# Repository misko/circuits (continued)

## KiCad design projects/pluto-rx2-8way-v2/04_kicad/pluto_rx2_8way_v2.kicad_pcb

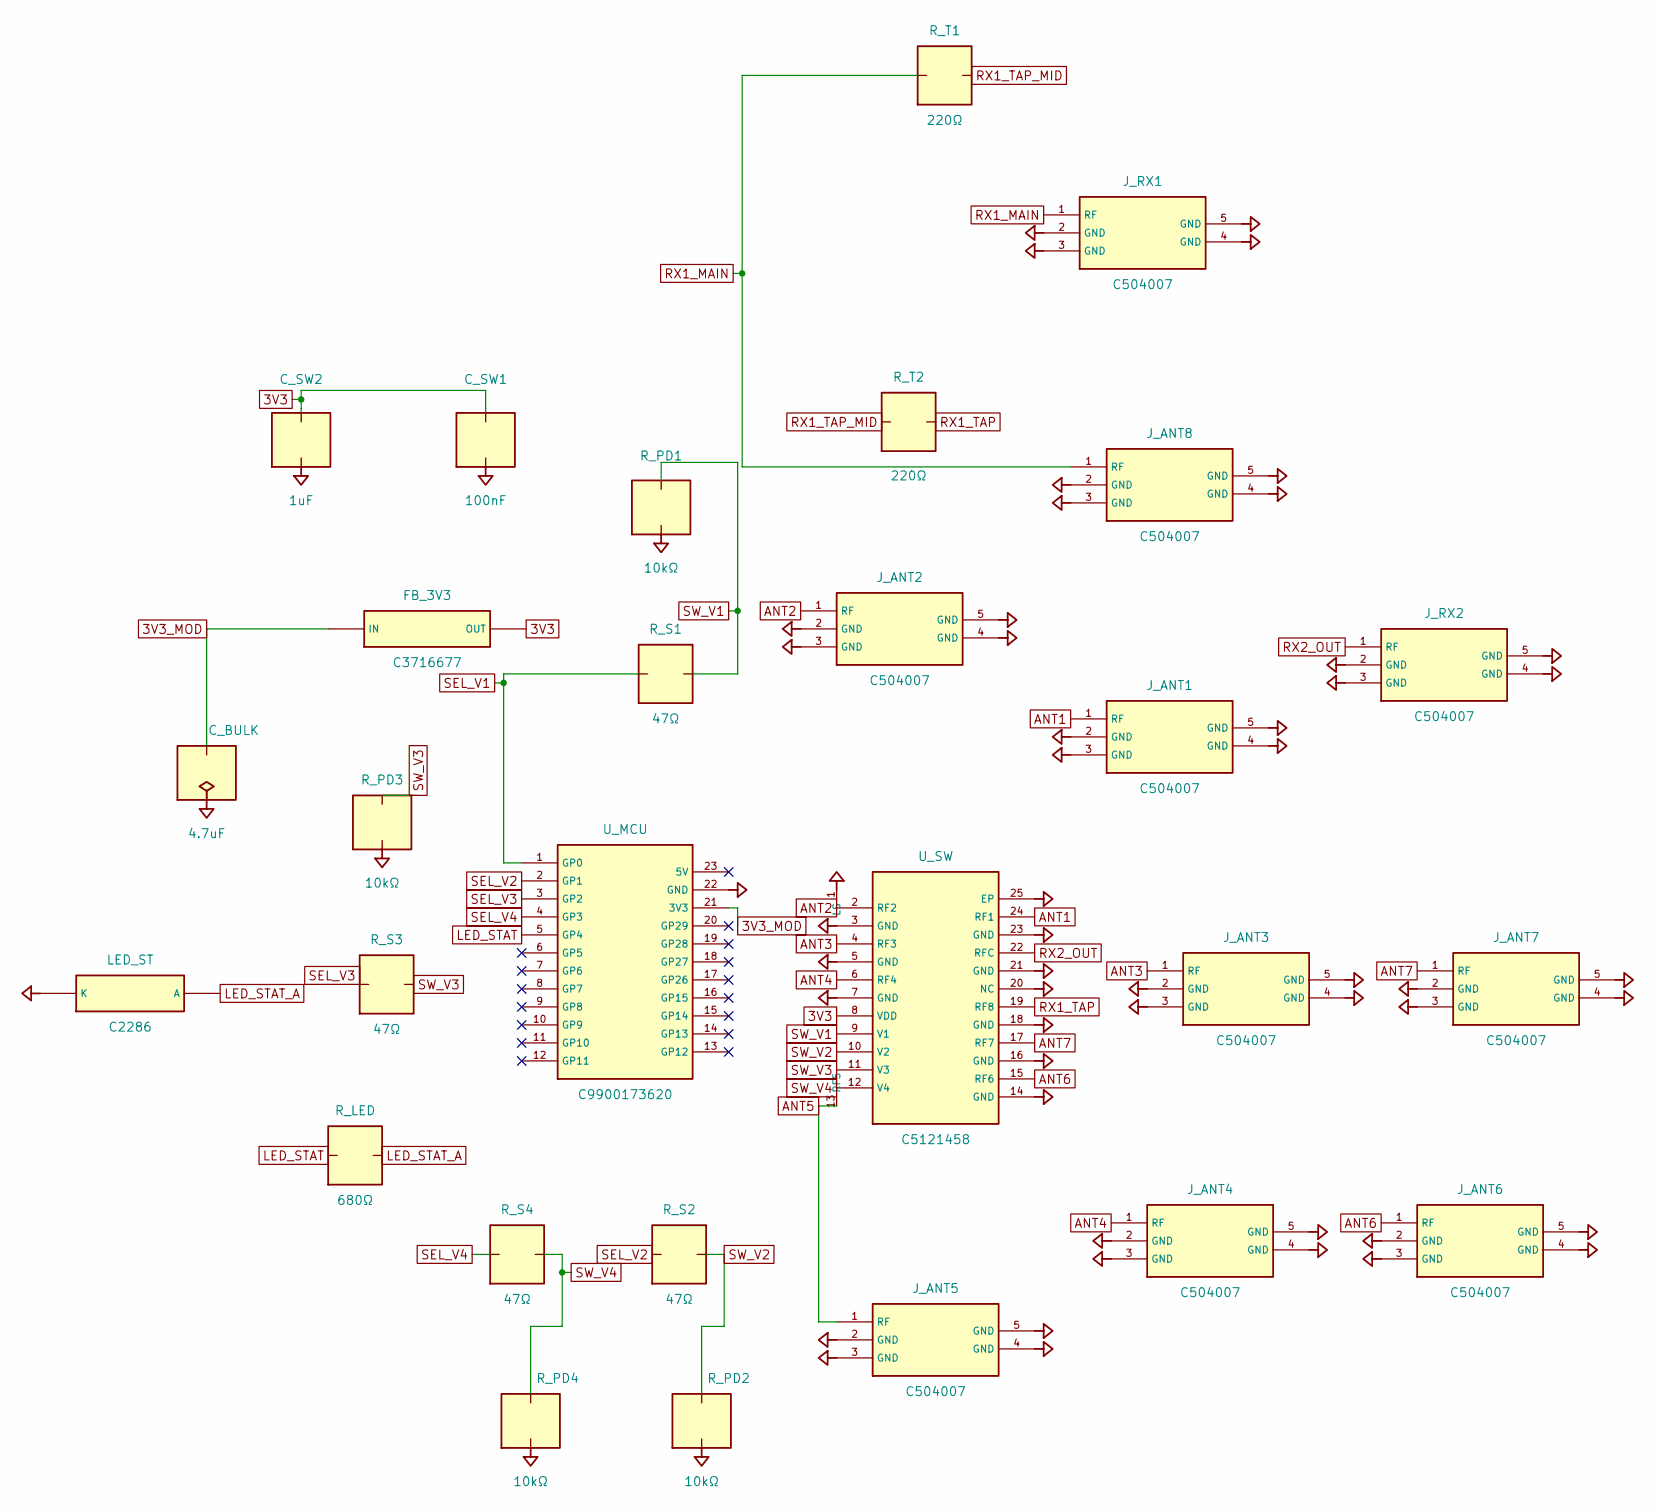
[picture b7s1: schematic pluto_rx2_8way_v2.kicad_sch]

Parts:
C_BULK: 4.7uF; C_0805_2012Metric
C_SW1: 100nF; C_0402_1005Metric
C_SW2: 1uF; C_0603_1608Metric
FB_3V3: C3716677; L_0805_2012Metric
J_ANT1, J_ANT2, J_ANT3, J_ANT4, J_ANT5, J_ANT6, J_ANT7, J_ANT8: C504007; SMA_Vertical_5.08sq_D1.4
J_RX1, J_RX2: C504007; SMA_Vertical_5.08sq_D1.4
LED_ST: C2286; LED_0603_1608Metric
R_LED: 680Ω; R_0402_1005Metric
R_PD1, R_PD2, R_PD3, R_PD4: 10kΩ; R_0402_1005Metric
R_S1, R_S2, R_S3, R_S4: 47Ω; R_0402_1005Metric
R_T1, R_T2: 220Ω; R_0402_1005Metric
U_MCU: C9900173620; RP2040_Zero_LCC23_18x23.5
U_SW: C5121458; QFN-24_4x4_P0.5_EP2.7_PE42482

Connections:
3V3: C_SW1.1, C_SW2.1, FB_3V3.2 (OUT), U_SW.8 (VDD)
3V3_MOD: C_BULK.1, FB_3V3.1 (IN), U_MCU.21 (3V3)
ANT1: J_ANT1.1 (RF), U_SW.24 (RF1)
ANT2: J_ANT2.1 (RF), U_SW.2 (RF2)
ANT3: J_ANT3.1 (RF), U_SW.4 (RF3)
ANT4: J_ANT4.1 (RF), U_SW.6 (RF4)
ANT5: J_ANT5.1 (RF), U_SW.13 (RF5)
ANT6: J_ANT6.1 (RF), U_SW.15 (RF6)
ANT7: J_ANT7.1 (RF), U_SW.17 (RF7)
GND: C_BULK.2, C_SW1.2, C_SW2.2, J_ANT1.2 (GND), J_ANT1.3 (GND), J_ANT1.4 (GND), J_ANT1.5 (GND), J_ANT2.2 (GND), J_ANT2.3 (GND), J_ANT2.4 (GND), J_ANT2.5 (GND), J_ANT3.2 (GND), J_ANT3.3 (GND), J_ANT3.4 (GND), J_ANT3.5 (GND), J_ANT4.2 (GND), J_ANT4.3 (GND), J_ANT4.4 (GND), J_ANT4.5 (GND), J_ANT5.2 (GND), J_ANT5.3 (GND), J_ANT5.4 (GND), J_ANT5.5 (GND), J_ANT6.2 (GND), J_ANT6.3 (GND), J_ANT6.4 (GND), J_ANT6.5 (GND), J_ANT7.2 (GND), J_ANT7.3 (GND), J_ANT7.4 (GND), J_ANT7.5 (GND), J_ANT8.2 (GND), J_ANT8.3 (GND), J_ANT8.4 (GND), J_ANT8.5 (GND), J_RX1.2 (GND), J_RX1.3 (GND), J_RX1.4 (GND), J_RX1.5 (GND), J_RX2.2 (GND), J_RX2.3 (GND), J_RX2.4 (GND), J_RX2.5 (GND), LED_ST.1 (K), R_PD1.2, R_PD2.2, R_PD3.2, R_PD4.2, U_MCU.22 (GND), U_SW.1 (LS), U_SW.3 (GND), U_SW.5 (GND), U_SW.7 (GND), U_SW.14 (GND), U_SW.16 (GND), U_SW.18 (GND), U_SW.20 (NC), U_SW.21 (GND), U_SW.23 (GND), U_SW.25 (EP)
LED_STAT: R_LED.1, U_MCU.5 (GP4)
LED_STAT_A: LED_ST.2 (A), R_LED.2
RX1_MAIN: J_ANT8.1 (RF), J_RX1.1 (RF), R_T1.1
RX1_TAP: R_T2.2, U_SW.19 (RF8)
RX1_TAP_MID: R_T1.2, R_T2.1
RX2_OUT: J_RX2.1 (RF), U_SW.22 (RFC)
SEL_V1: R_S1.1, U_MCU.1 (GP0)
SEL_V2: R_S2.1, U_MCU.2 (GP1)
SEL_V3: R_S3.1, U_MCU.3 (GP2)
SEL_V4: R_S4.1, U_MCU.4 (GP3)
SW_V1: R_PD1.1, R_S1.2, U_SW.9 (V1)
SW_V2: R_PD2.1, R_S2.2, U_SW.10 (V2)
SW_V3: R_PD3.1, R_S3.2, U_SW.11 (V3)
SW_V4: R_PD4.1, R_S4.2, U_SW.12 (V4)

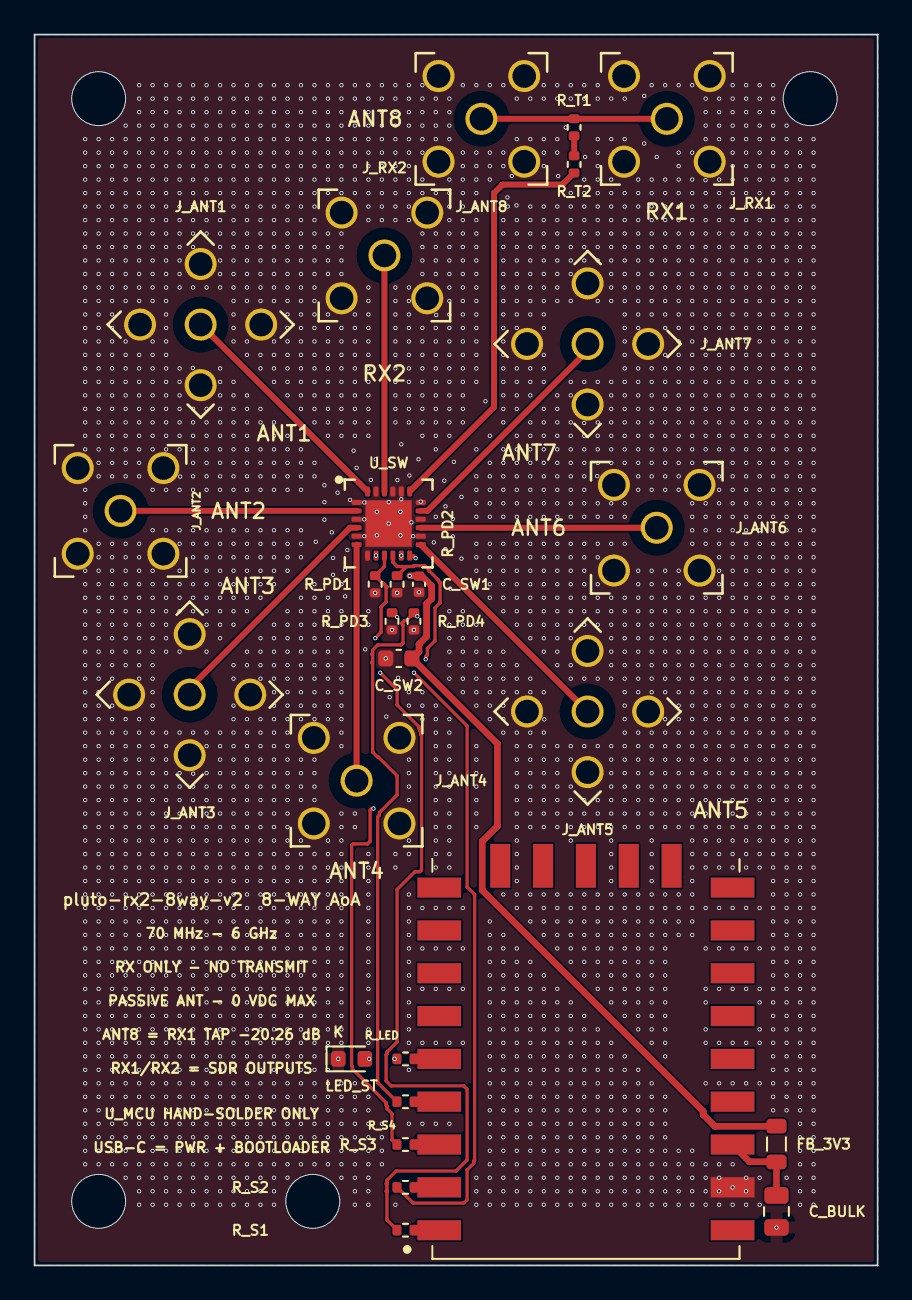
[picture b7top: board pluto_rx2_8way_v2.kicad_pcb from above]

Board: 4 copper layers, 50.0 x 73.0 mm, 32 parts (0 on the bottom side), 24 nets.

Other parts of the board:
H1, H2, H3, H4: MountingHole_3.2mm_M3

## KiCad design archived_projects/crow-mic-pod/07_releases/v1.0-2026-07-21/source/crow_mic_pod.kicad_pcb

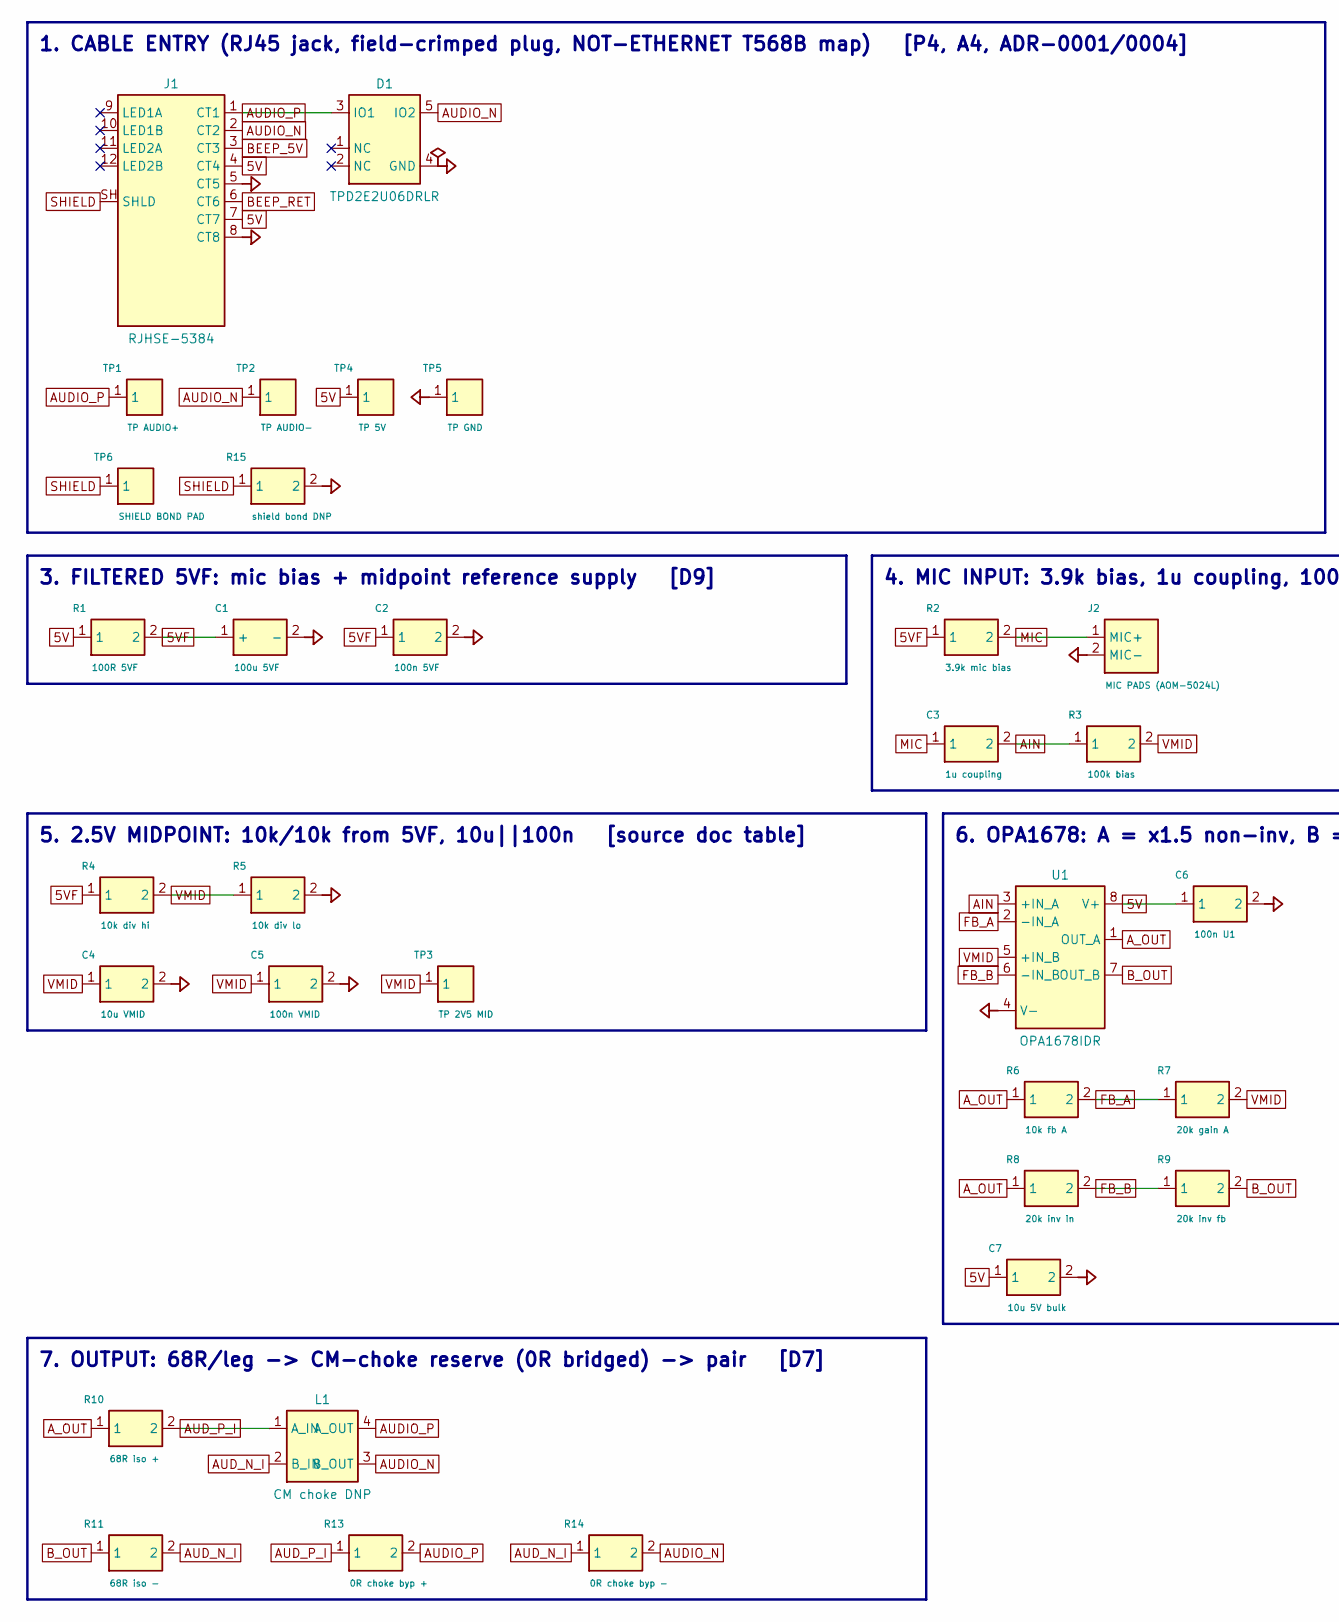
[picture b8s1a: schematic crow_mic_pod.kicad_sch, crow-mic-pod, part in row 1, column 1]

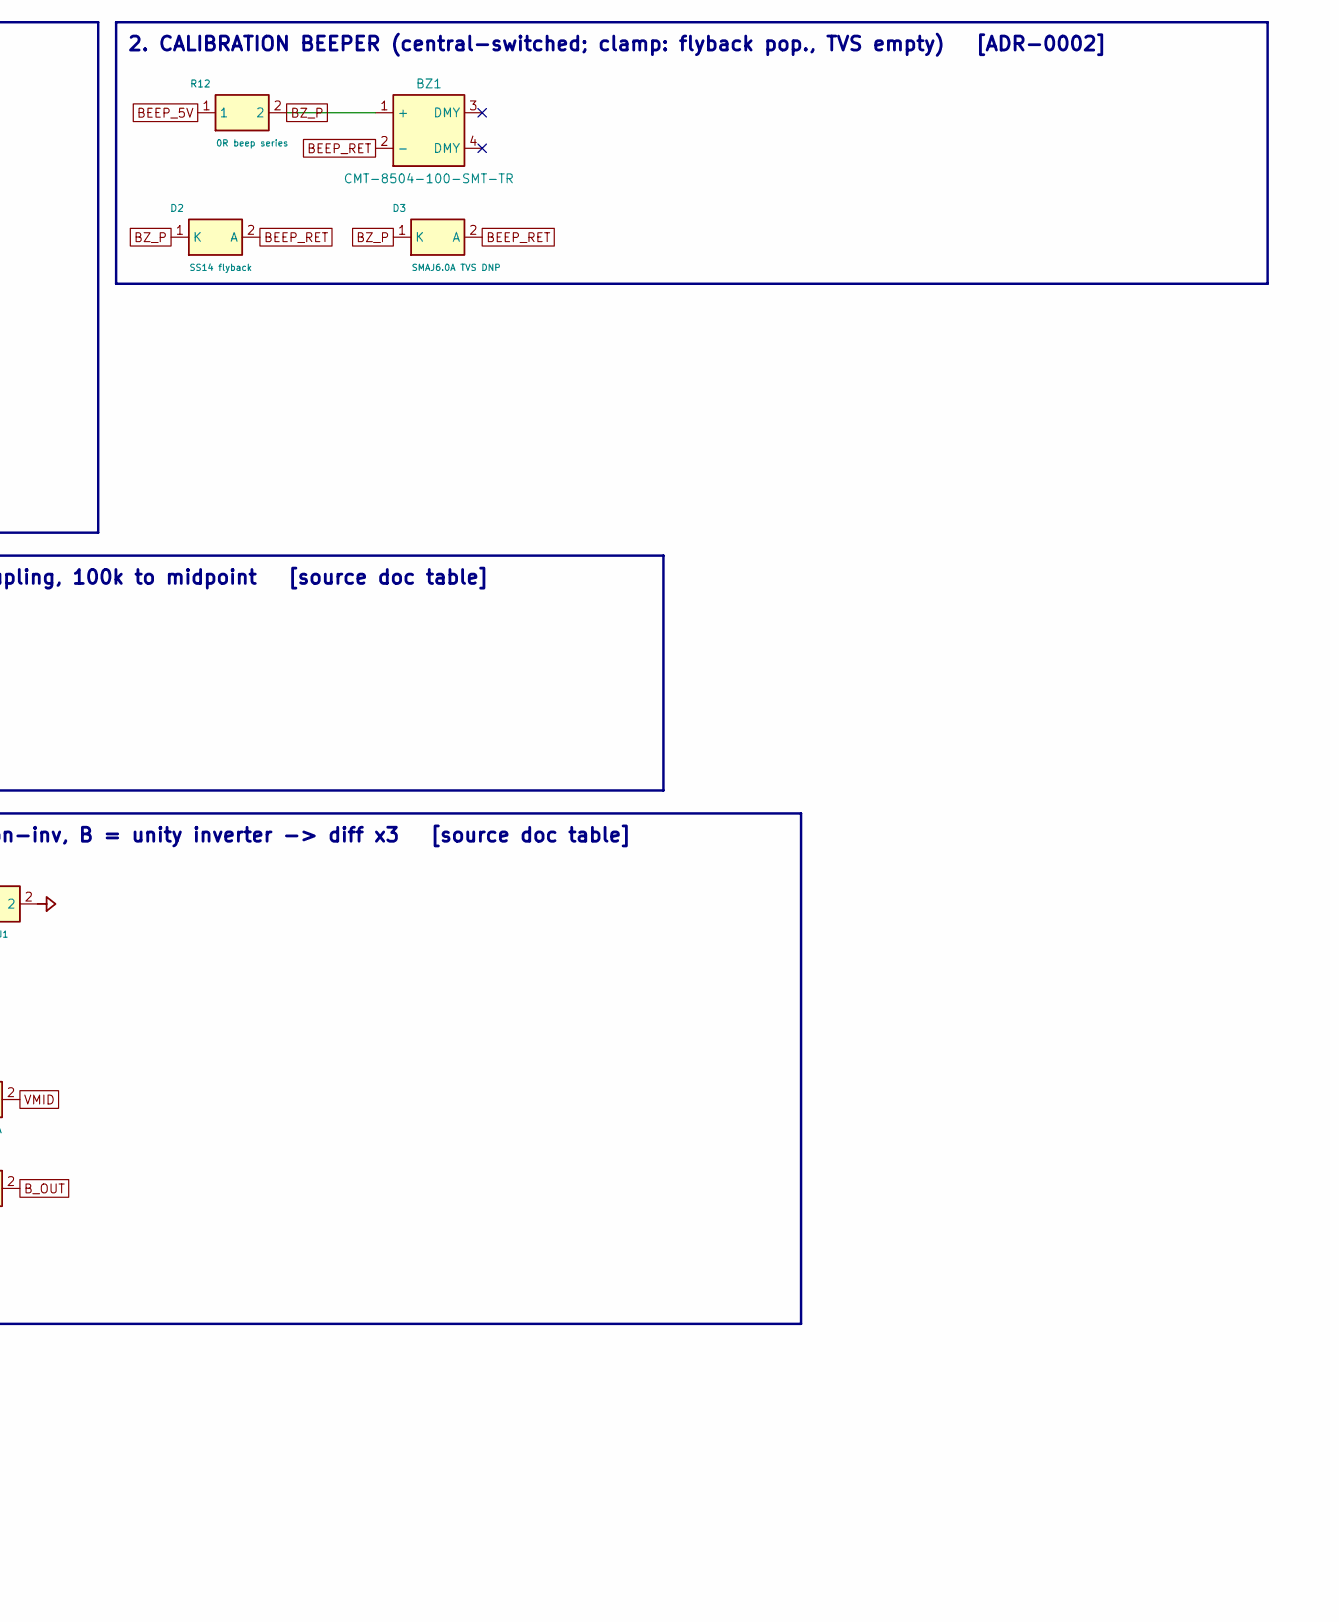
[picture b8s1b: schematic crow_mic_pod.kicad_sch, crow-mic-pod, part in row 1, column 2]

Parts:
BZ1: CMT-8504-100-SMT-TR; CMT-8504
C1: 100u 5VF; CP_Elec_6.3x5.4
C2: 100n 5VF; C_0805_2012Metric
C3: 1u coupling; C_0805_2012Metric
C4: 10u VMID; C_0805_2012Metric
C5: 100n VMID; C_0805_2012Metric
C6: 100n U1; C_0805_2012Metric
C7: 10u 5V bulk; C_0805_2012Metric
D1: TPD2E2U06DRLR; SOT-553
D2: SS14 flyback; D_SMA
D3: SMAJ6.0A TVS DNP; D_SMA
J1: RJHSE-5384; RJ45_Amphenol_RJHSE538X
J2: MIC PADS (AOM-5024L); PinHeader_1x02_P2.54mm_Vertical
L1: CM choke DNP; L_CommonMode_Wuerth_WE-SL2
R1: 100R 5VF; R_0805_2012Metric
R2: 3.9k mic bias; R_0805_2012Metric
R3: 100k bias; R_0805_2012Metric
R4: 10k div hi; R_0805_2012Metric
R5: 10k div lo; R_0805_2012Metric
R6: 10k fb A; R_0805_2012Metric
R7: 20k gain A; R_0805_2012Metric
R8: 20k inv in; R_0805_2012Metric
R9: 20k inv fb; R_0805_2012Metric
R10: 68R iso +; R_0805_2012Metric
R11: 68R iso -; R_0805_2012Metric
R12: 0R beep series; R_0805_2012Metric
R13: 0R choke byp +; R_0805_2012Metric
R14: 0R choke byp -; R_0805_2012Metric
R15: shield bond DNP; R_0805_2012Metric
TP1: TP AUDIO+; TestPoint_Pad_D1.5mm
TP2: TP AUDIO-; TestPoint_Pad_D1.5mm
TP3: TP 2V5 MID; TestPoint_Pad_D1.5mm
TP4: TP 5V; TestPoint_Pad_D1.5mm
TP5: TP GND; TestPoint_Pad_D1.5mm
TP6: SHIELD BOND PAD; TestPoint_Pad_D2.5mm
U1: OPA1678IDR; SOIC-8_3.9x4.9mm_P1.27mm

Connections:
5V: C6.1, C7.1, J1.4 (CT4), J1.7 (CT7), R1.1, TP4.1, U1.8 (V+)
5VF: C1.1 (+), C2.1, R1.2, R2.1, R4.1
AIN: C3.2, R3.1, U1.3 (+IN_A)
AUDIO_N: D1.5 (IO2), J1.2 (CT2), L1.3 (B_OUT), R14.2, TP2.1
AUDIO_P: D1.3 (IO1), J1.1 (CT1), L1.4 (A_OUT), R13.2, TP1.1
AUD_N_I: L1.2 (B_IN), R11.2, R14.1
AUD_P_I: L1.1 (A_IN), R10.2, R13.1
A_OUT: R6.1, R8.1, R10.1, U1.1 (OUT_A)
BEEP_5V: J1.3 (CT3), R12.1
BEEP_RET: BZ1.2 (-), D2.2 (A), D3.2 (A), J1.6 (CT6)
BZ_P: BZ1.1 (+), D2.1 (K), D3.1 (K), R12.2
B_OUT: R9.2, R11.1, U1.7 (OUT_B)
FB_A: R6.2, R7.1, U1.2 (-IN_A)
FB_B: R8.2, R9.1, U1.6 (-IN_B)
GND: C1.2 (-), C2.2, C4.2, C5.2, C6.2, C7.2, D1.4 (GND), J1.5 (CT5), J1.8 (CT8), J2.2 (MIC-), R5.2, R15.2, TP5.1, U1.4 (V-)
MIC: C3.1, J2.1 (MIC+), R2.2
SHIELD: J1.SH (SHLD), R15.1, TP6.1
VMID: C4.1, C5.1, R3.2, R4.2, R5.1, R7.2, TP3.1, U1.5 (+IN_B)

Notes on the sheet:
1. CABLE ENTRY (RJ45 jack, field-crimped plug, NOT-ETHERNET T568B map) [P4, A4, ADR-0001/0004]
2. CALIBRATION BEEPER (central-switched; clamp: flyback pop., TVS empty) [ADR-0002]
3. FILTERED 5VF: mic bias + midpoint reference supply [D9]
4. MIC INPUT: 3.9k bias, 1u coupling, 100k to midpoint [source doc table]
5. 2.5V MIDPOINT: 10k/10k from 5VF, 10u||100n [source doc table]
6. OPA1678: A = x1.5 non-inv, B = unity inverter -> diff x3 [source doc table]
7. OUTPUT: 68R/leg -> CM-choke reserve (0R bridged) -> pair [D7]

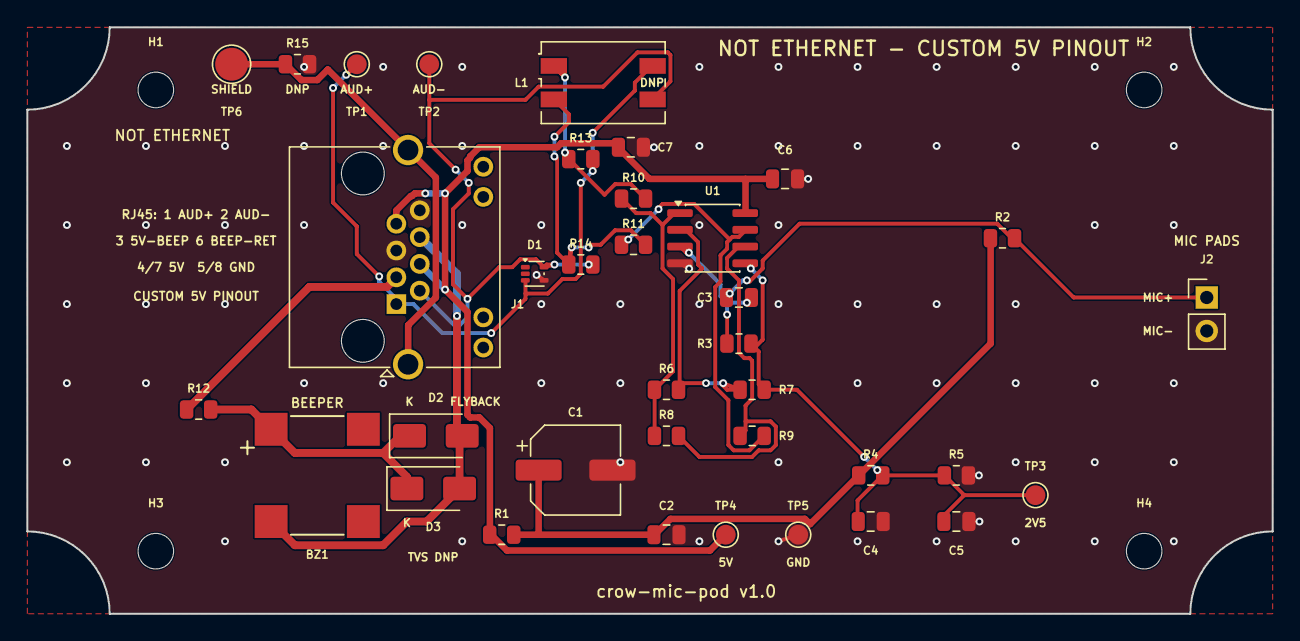
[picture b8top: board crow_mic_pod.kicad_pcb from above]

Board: 2 copper layers, 94.5 x 44.5 mm, 40 parts (0 on the bottom side), 18 nets.

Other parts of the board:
H1, H2, H3, H4: MountingHole_2.7mm_M2.5
